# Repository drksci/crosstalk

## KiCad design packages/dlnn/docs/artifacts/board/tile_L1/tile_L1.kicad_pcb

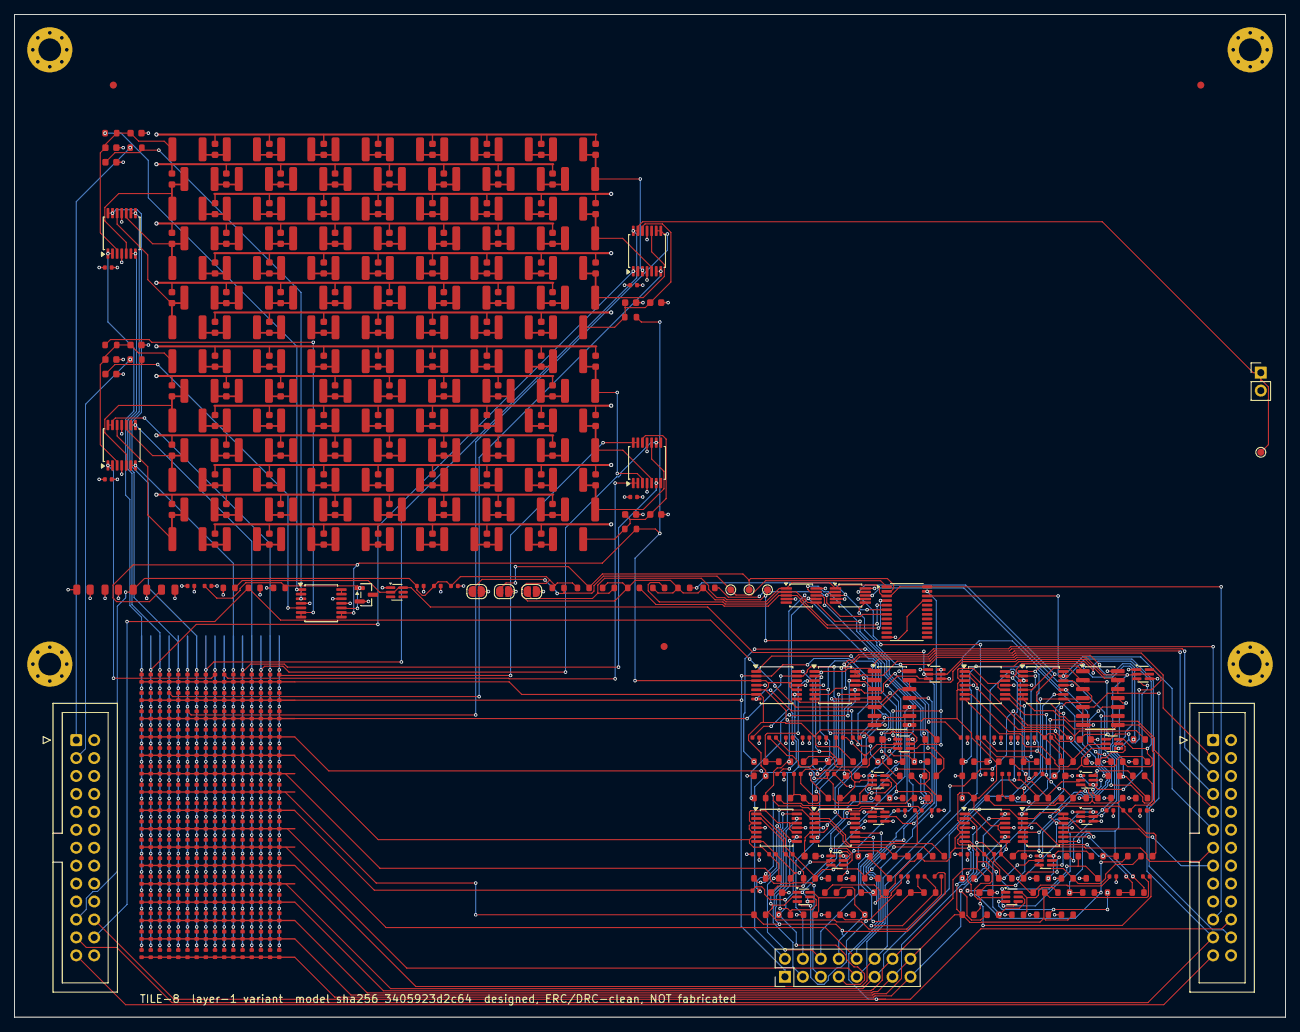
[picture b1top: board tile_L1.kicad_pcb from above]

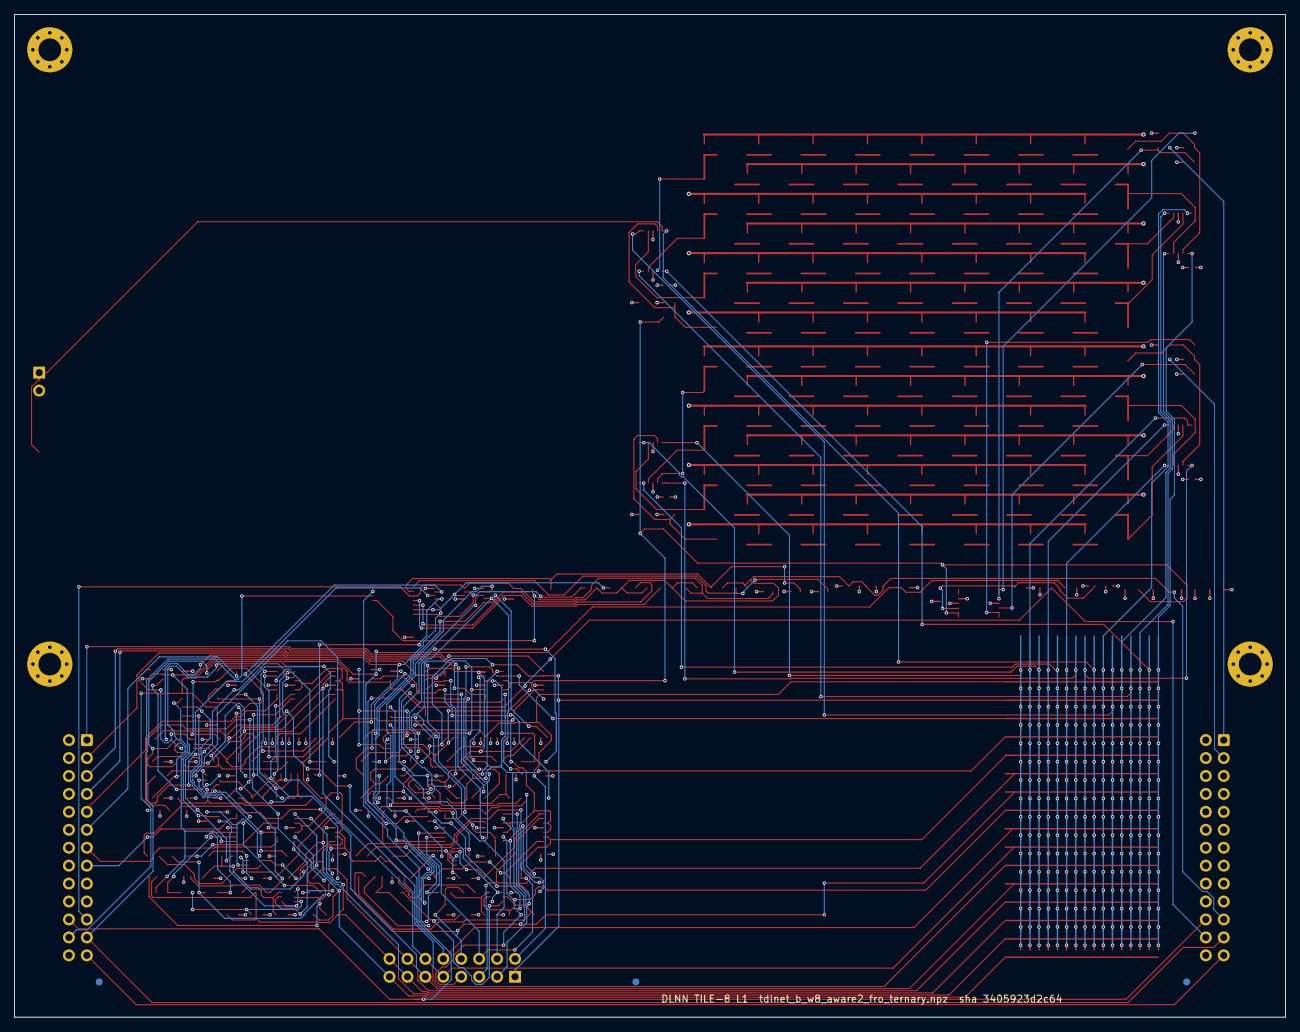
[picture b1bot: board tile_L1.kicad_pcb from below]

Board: 4 copper layers, 180.0 x 142.0 mm, 700 parts (3 on the bottom side), 258 nets.

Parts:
C0_0_1, C0_0_2, C0_56_1, C0_56_2, C1_0_1, C1_0_2, C1_56_1, C1_56_2: 30p; C_0603_1608Metric
C0_1, C0_2, C0_3, C0_4, C0_5, C0_6, C0_7, C0_8, C0_9, C0_10, C0_11, C0_12, C0_13, C0_14, C0_15, C0_16, C0_17, C0_18, C0_19, C0_20, C0_21, C0_22, C0_23, C0_24, C0_25, C0_26, C0_27, C0_28, C0_29, C0_30, C0_31, C0_32, C0_33, C0_34, C0_35, C0_36, C0_37, C0_38, C0_39, C0_40, C0_41, C0_42, C0_43, C0_44, C0_45, C0_46, C0_47, C0_48, C0_49, C0_50, C0_51, C0_52, C0_53, C0_54, C0_55, C1_1, C1_2, C1_3, C1_4, C1_5, C1_6, C1_7, C1_8, C1_9, C1_10, C1_11, C1_12, C1_13, C1_14, C1_15, C1_16, C1_17, C1_18, C1_19, C1_20, C1_21, C1_22, C1_23, C1_24, C1_25, C1_26, C1_27, C1_28, C1_29, C1_30, C1_31, C1_32, C1_33, C1_34, C1_35, C1_36, C1_37, C1_38, C1_39, C1_40, C1_41, C1_42, C1_43, C1_44, C1_45, C1_46, C1_47, C1_48, C1_49, C1_50, C1_51, C1_52, C1_53, C1_54, C1_55: 120p; C_0603_1608Metric
CB1, CB2, CB3, CB4: 10u; C_0805_2012Metric
CBF0, CBF1, CBF2, CBF3, CBF4, CBF5, CBF6, CBF7: 100n; C_0402_1005Metric
CDA0, CDA1, CDA2, CDA3, CDA4, CDA5, CDA6, CDA7: 8.2p; C_0402_1005Metric
CDCS0, CDCS1, CDCS2, CDCS3: 100n; C_0402_1005Metric
CDDA0, CDDA1, CDDA2, CDDA3: 100n; C_0402_1005Metric
CDDAC0, CDDAC1: 100n; C_0402_1005Metric
CDIB0: 100n; C_0402_1005Metric
CDMUX1: 100n; C_0402_1005Metric
CDSH0, CDSH1: 100n; C_0402_1005Metric
CDTA0, CDTA1: 100n; C_0402_1005Metric
CDTB0, CDTB1: 100n; C_0402_1005Metric
CFN0, CFN1, CFN2, CFN3, CFN4, CFN5, CFN6, CFN7: 15p; C_0402_1005Metric
CFP0, CFP1, CFP2, CFP3, CFP4, CFP5, CFP6, CFP7: 15p; C_0402_1005Metric
CH0, CH1, CH2, CH3, CH4, CH5, CH6, CH7: 560p; C_0603_1608Metric
CP0, CP1: 330p; C_0603_1608Metric
CREF1: 100n; C_0402_1005Metric
FID1, FID2, FID3, FID4, FID5, FID6: Fiducial_1mm_Mask2mm
H1, H2, H3, H4: MountingHole_3.2mm_M3_Pad_Via
JIN1: 2x13 IDC; IDC-Header_2x13_P2.54mm_Vertical
JMON1: MON; PinHeader_1x02_P2.54mm_Vertical
JOUT1: 2x13 IDC; IDC-Header_2x13_P2.54mm_Vertical
JPID0, JPID1, JPID2: ID; SolderJumper-2_P1.3mm_Open_RoundedPad1.0x1.5mm
JPS1: J_PS 2x8; PinHeader_2x08_P2.54mm_Vertical
L0_1, L0_2, L0_3, L0_4, L0_5, L0_6, L0_7, L0_8, L0_9, L0_10, L0_11, L0_12, L0_13, L0_14, L0_15, L0_16, L0_17, L0_18, L0_19, L0_20, L0_21, L0_22, L0_23, L0_24, L0_25, L0_26, L0_27, L0_28, L0_29, L0_30, L0_31, L0_32, L0_33, L0_34, L0_35, L0_36, L0_37, L0_38, L0_39, L0_40, L0_41, L0_42, L0_43, L0_44, L0_45, L0_46, L0_47, L0_48, L0_49, L0_50, L0_51, L0_52, L0_53, L0_54, L0_55, L0_56, L1_1, L1_2, L1_3, L1_4, L1_5, L1_6, L1_7, L1_8, L1_9, L1_10, L1_11, L1_12, L1_13, L1_14, L1_15, L1_16, L1_17, L1_18, L1_19, L1_20, L1_21, L1_22, L1_23, L1_24, L1_25, L1_26, L1_27, L1_28, L1_29, L1_30, L1_31, L1_32, L1_33, L1_34, L1_35, L1_36, L1_37, L1_38, L1_39, L1_40, L1_41, L1_42, L1_43, L1_44, L1_45, L1_46, L1_47, L1_48, L1_49, L1_50, L1_51, L1_52, L1_53, L1_54, L1_55, L1_56: 120u; L_1812_4532Metric
QD0, QD1, QD2, QD3, QD4, QD5, QD6, QD7: BCM847BS; SOT-363_SC-70-6
RB0, RB1, RB2, RB3, RB4, RB5, RB6, RB7: 15k; R_0603_1608Metric
RDA1_0, RDA1_1, RDA1_2, RDA1_3, RDA1_4, RDA1_5, RDA1_6, RDA1_7, RDA3_0, RDA3_1, RDA3_2, RDA3_3, RDA3_4, RDA3_5, RDA3_6, RDA3_7: 20k; R_0603_1608Metric
RDA2_0, RDA2_1, RDA2_2, RDA2_3, RDA2_4, RDA2_5, RDA2_6, RDA2_7, RDA4_0, RDA4_1, RDA4_2, RDA4_3, RDA4_4, RDA4_5, RDA4_6, RDA4_7: 10.5k; R_0603_1608Metric
RFN0, RFN1, RFN2, RFN3, RFN4, RFN5, RFN6, RFN7: 2.21k; R_0603_1608Metric
RFP0, RFP1, RFP2, RFP3, RFP4, RFP5, RFP6, RFP7: 2.21k; R_0603_1608Metric
RID0, RID1, RID2: 10k; R_0603_1608Metric
RLD1_0, RLD1_1, RLD1_2, RLD1_3, RLD1_4, RLD1_5, RLD1_6, RLD1_7, RLD2_0, RLD2_1, RLD2_2, RLD2_3, RLD2_4, RLD2_5, RLD2_6, RLD2_7: 1k; R_0603_1608Metric
RMIR1: 4.32k; R_0603_1608Metric
RO0, RO1, RO2, RO3, RO4, RO5, RO6, RO7: 25.5k; R_0603_1608Metric
RP0, RP1: 1k; R_0603_1608Metric
RPD1: 10k; R_0603_1608Metric
RPU1, RPU2, RPU3, RPU4: 10k; R_0603_1608Metric
RREF1: 2.49k; R_0603_1608Metric
RS0, RS1: 1k; R_0603_1608Metric
RT0, RT1: 1k; R_0603_1608Metric
RXN_0_0_0, RXN_0_0_1, RXN_0_0_2, RXN_0_0_3, RXN_0_0_4, RXN_0_0_5, RXN_0_0_6, RXN_0_0_7, RXN_0_1_0, RXN_0_1_1, RXN_0_1_2, RXN_0_1_3, RXN_0_1_4, RXN_0_1_5, RXN_0_1_6, RXN_0_1_7, RXN_1_0_0, RXN_1_0_1, RXN_1_0_2, RXN_1_0_3, RXN_1_0_4, RXN_1_0_5, RXN_1_0_6, RXN_1_0_7, RXN_1_1_0, RXN_1_1_1, RXN_1_1_2, RXN_1_1_3, RXN_1_1_4, RXN_1_1_5, RXN_1_1_6, RXN_1_1_7, RXN_2_0_0, RXN_2_0_1, RXN_2_0_2, RXN_2_0_3, RXN_2_0_4, RXN_2_0_5, RXN_2_0_6, RXN_2_0_7, RXN_2_1_0, RXN_2_1_1, RXN_2_1_2, RXN_2_1_3, RXN_2_1_4, RXN_2_1_5, RXN_2_1_6, RXN_2_1_7, RXN_3_0_0, RXN_3_0_1, RXN_3_0_2, RXN_3_0_3, RXN_3_0_4, RXN_3_0_5, RXN_3_0_6, RXN_3_0_7, RXN_3_1_0, RXN_3_1_1, RXN_3_1_2, RXN_3_1_3, RXN_3_1_4, RXN_3_1_5, RXN_3_1_6, RXN_3_1_7, RXN_4_0_0, RXN_4_0_1, RXN_4_0_2, RXN_4_0_3, RXN_4_0_4, RXN_4_0_5, RXN_4_0_6, RXN_4_0_7, RXN_4_1_0, RXN_4_1_1, RXN_4_1_2, RXN_4_1_3, RXN_4_1_4, RXN_4_1_5, RXN_4_1_6, RXN_4_1_7, RXN_5_0_0, RXN_5_0_1, RXN_5_0_2, RXN_5_0_3, RXN_5_0_4, RXN_5_0_5, RXN_5_0_6, RXN_5_0_7, RXN_5_1_0, RXN_5_1_1, RXN_5_1_2, RXN_5_1_3, RXN_5_1_4, RXN_5_1_5, RXN_5_1_6, RXN_5_1_7, RXN_6_0_0, RXN_6_0_1, RXN_6_0_2, RXN_6_0_3, RXN_6_0_4, RXN_6_0_5, RXN_6_0_6, RXN_6_0_7, RXN_6_1_0, RXN_6_1_1, RXN_6_1_2, RXN_6_1_3, RXN_6_1_4, RXN_6_1_5, RXN_6_1_6, RXN_6_1_7, RXN_7_0_0, RXN_7_0_1, RXN_7_0_2, RXN_7_0_3, RXN_7_0_4, RXN_7_0_5, RXN_7_0_6, RXN_7_0_7, RXN_7_1_0, RXN_7_1_1, RXN_7_1_2, RXN_7_1_3, RXN_7_1_4, RXN_7_1_5, RXN_7_1_6, RXN_7_1_7: 10k; R_0402_1005Metric
RXP_0_0_0, RXP_0_0_1, RXP_0_0_2, RXP_0_0_3, RXP_0_0_4, RXP_0_0_5, RXP_0_0_6, RXP_0_0_7, RXP_0_1_0, RXP_0_1_1, RXP_0_1_2, RXP_0_1_3, RXP_0_1_4, RXP_0_1_5, RXP_0_1_6, RXP_0_1_7, RXP_1_0_0, RXP_1_0_1, RXP_1_0_2, RXP_1_0_3, RXP_1_0_4, RXP_1_0_5, RXP_1_0_6, RXP_1_0_7, RXP_1_1_0, RXP_1_1_1, RXP_1_1_2, RXP_1_1_3, RXP_1_1_4, RXP_1_1_5, RXP_1_1_6, RXP_1_1_7, RXP_2_0_0, RXP_2_0_1, RXP_2_0_2, RXP_2_0_3, RXP_2_0_4, RXP_2_0_5, RXP_2_0_6, RXP_2_0_7, RXP_2_1_0, RXP_2_1_1, RXP_2_1_2, RXP_2_1_3, RXP_2_1_4, RXP_2_1_5, RXP_2_1_6, RXP_2_1_7, RXP_3_0_0, RXP_3_0_1, RXP_3_0_2, RXP_3_0_3, RXP_3_0_4, RXP_3_0_5, RXP_3_0_6, RXP_3_0_7, RXP_3_1_0, RXP_3_1_1, RXP_3_1_2, RXP_3_1_3, RXP_3_1_4, RXP_3_1_5, RXP_3_1_6, RXP_3_1_7, RXP_4_0_0, RXP_4_0_1, RXP_4_0_2, RXP_4_0_3, RXP_4_0_4, RXP_4_0_5, RXP_4_0_6, RXP_4_0_7, RXP_4_1_0, RXP_4_1_1, RXP_4_1_2, RXP_4_1_3, RXP_4_1_4, RXP_4_1_5, RXP_4_1_6, RXP_4_1_7, RXP_5_0_0, RXP_5_0_1, RXP_5_0_2, RXP_5_0_3, RXP_5_0_4, RXP_5_0_5, RXP_5_0_6, RXP_5_0_7, RXP_5_1_0, RXP_5_1_1, RXP_5_1_2, RXP_5_1_3, RXP_5_1_4, RXP_5_1_5, RXP_5_1_6, RXP_5_1_7, RXP_6_0_0, RXP_6_0_1, RXP_6_0_2, RXP_6_0_3, RXP_6_0_4, RXP_6_0_5, RXP_6_0_6, RXP_6_0_7, RXP_6_1_0, RXP_6_1_1, RXP_6_1_2, RXP_6_1_3, RXP_6_1_4, RXP_6_1_5, RXP_6_1_6, RXP_6_1_7, RXP_7_0_0, RXP_7_0_1, RXP_7_0_2, RXP_7_0_3, RXP_7_0_4, RXP_7_0_5, RXP_7_0_6, RXP_7_0_7, RXP_7_1_0, RXP_7_1_1, RXP_7_1_2, RXP_7_1_3, RXP_7_1_4, RXP_7_1_5, RXP_7_1_6, RXP_7_1_7: 10k; R_0402_1005Metric
TPID0: TID0; TestPoint_Pad_D1.0mm
TPID1: TID1; TestPoint_Pad_D1.0mm
TPID2: TID2; TestPoint_Pad_D1.0mm
TPMON1: MON; TestPoint_Pad_D1.0mm
UCS0, UCS1, UCS2, UCS3: TLV9064IPW; TSSOP-14_4.4x5mm_P0.65mm
UDA0, UDA1, UDA2, UDA3: TLV9064IPW; TSSOP-14_4.4x5mm_P0.65mm
UDAC0, UDAC1: MCP4728; MSOP-10_3x3mm_P0.5mm
UIB0: TLV9064IPW; TSSOP-14_4.4x5mm_P0.65mm
UMUX1: TCA9548APWR; TSSOP-24_4.4x7.8mm_P0.65mm
UREF1: LM4040B25FTA; SOT-23
USH0, USH1: 74HCT4066; SOIC-14_3.9x8.7mm_P1.27mm
UT0, UT1, UT2, UT3: BC847BS; SOT-363_SC-70-6
UTA0, UTA1: TLV9064IPW; TSSOP-14_4.4x5mm_P0.65mm
UTB0, UTB1: TLV9064IPW; TSSOP-14_4.4x5mm_P0.65mm
UTR1: BC847BS; SOT-363_SC-70-6

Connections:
+3V3: CB3.1, CDDAC0.1, CDDAC1.1, CDMUX1.1, JIN1.21, JOUT1.21, RID0.1, RID1.1, RID2.1, RPU1.1, RPU2.1, RPU3.1, RPU4.1, UDAC0.1, UDAC1.1, UMUX1.3, UMUX1.24
+5VA: CB1.1, CB2.1, CDCS0.1, CDCS1.1, CDCS2.1, CDCS3.1, CDDA0.1, CDDA1.1, CDDA2.1, CDDA3.1, CDIB0.1, CDSH0.1, CDSH1.1, CDTA0.1, CDTA1.1, CDTB0.1, CDTB1.1, JIN1.17, JIN1.19, JOUT1.17, JOUT1.19, RLD1_0.1, RLD1_1.1, RLD1_2.1, RLD1_3.1, RLD1_4.1, RLD1_5.1, RLD1_6.1, RLD1_7.1, RLD2_0.1, RLD2_1.1, RLD2_2.1, RLD2_3.1, RLD2_4.1, RLD2_5.1, RLD2_6.1, RLD2_7.1, RMIR1.1, RO0.1, RO1.1, RO2.1, RO3.1, RO4.1, RO5.1, RO6.1, RO7.1, RREF1.1, UCS0.4, UCS1.4, UCS2.4, UCS3.4, UDA0.4, UDA1.4, UDA2.4, UDA3.4, UIB0.4, USH0.14, USH1.14, UTA0.4, UTA1.4, UTB0.4, UTB1.4
/ch0/DAIN: CDA0.1, RDA3_0.2, RDA4_0.1, UDA0.2
/ch0/DAIP: RDA1_0.2, RDA2_0.1, UDA0.3
/ch0/DAO: CDA0.2, RDA4_0.2, UDA0.1, USH0.1
/ch0/DC1: QD0.6, RDA1_0.1, RLD1_0.2
/ch0/DC2: QD0.3, RDA3_0.1, RLD2_0.2
/ch0/HOLD: CH0.1, UDA0.5, USH0.2
/ch0/ON: CFN0.2, QD0.2, RFN0.2, UCS0.7
/ch0/OP: CFP0.2, QD0.5, RFP0.2, UCS0.1
/ch0/TAIL: QD0.1, QD0.4, UT0.6
/ch1/DAIN: CDA1.1, RDA3_1.2, RDA4_1.1, UDA0.9
/ch1/DAIP: RDA1_1.2, RDA2_1.1, UDA0.10
/ch1/DAO: CDA1.2, RDA4_1.2, UDA0.8, USH0.4
/ch1/DC1: QD1.6, RDA1_1.1, RLD1_1.2
/ch1/DC2: QD1.3, RDA3_1.1, RLD2_1.2
/ch1/HOLD: CH1.1, UDA0.12, USH0.3
/ch1/ON: CFN1.2, QD1.2, RFN1.2, UCS0.14
/ch1/OP: CFP1.2, QD1.5, RFP1.2, UCS0.8
/ch1/TAIL: QD1.1, QD1.4, UT0.3
/ch2/DAIN: CDA2.1, RDA3_2.2, RDA4_2.1, UDA1.2
/ch2/DAIP: RDA1_2.2, RDA2_2.1, UDA1.3
/ch2/DAO: CDA2.2, RDA4_2.2, UDA1.1, USH0.8
/ch2/DC1: QD2.6, RDA1_2.1, RLD1_2.2
/ch2/DC2: QD2.3, RDA3_2.1, RLD2_2.2
/ch2/HOLD: CH2.1, UDA1.5, USH0.9
/ch2/ON: CFN2.2, QD2.2, RFN2.2, UCS1.7
/ch2/OP: CFP2.2, QD2.5, RFP2.2, UCS1.1
/ch2/TAIL: QD2.1, QD2.4, UT1.6
/ch3/DAIN: CDA3.1, RDA3_3.2, RDA4_3.1, UDA1.9
/ch3/DAIP: RDA1_3.2, RDA2_3.1, UDA1.10
/ch3/DAO: CDA3.2, RDA4_3.2, UDA1.8, USH0.11
/ch3/DC1: QD3.6, RDA1_3.1, RLD1_3.2
/ch3/DC2: QD3.3, RDA3_3.1, RLD2_3.2
/ch3/HOLD: CH3.1, UDA1.12, USH0.10
/ch3/ON: CFN3.2, QD3.2, RFN3.2, UCS1.14
/ch3/OP: CFP3.2, QD3.5, RFP3.2, UCS1.8
/ch3/TAIL: QD3.1, QD3.4, UT1.3
/ch4/DAIN: CDA4.1, RDA3_4.2, RDA4_4.1, UDA2.2
/ch4/DAIP: RDA1_4.2, RDA2_4.1, UDA2.3
/ch4/DAO: CDA4.2, RDA4_4.2, UDA2.1, USH1.1
/ch4/DC1: QD4.6, RDA1_4.1, RLD1_4.2
/ch4/DC2: QD4.3, RDA3_4.1, RLD2_4.2
/ch4/HOLD: CH4.1, UDA2.5, USH1.2
/ch4/ON: CFN4.2, QD4.2, RFN4.2, UCS2.7
/ch4/OP: CFP4.2, QD4.5, RFP4.2, UCS2.1
/ch4/TAIL: QD4.1, QD4.4, UT2.6
/ch5/DAIN: CDA5.1, RDA3_5.2, RDA4_5.1, UDA2.9
/ch5/DAIP: RDA1_5.2, RDA2_5.1, UDA2.10
/ch5/DAO: CDA5.2, RDA4_5.2, UDA2.8, USH1.4
/ch5/DC1: QD5.6, RDA1_5.1, RLD1_5.2
/ch5/DC2: QD5.3, RDA3_5.1, RLD2_5.2
/ch5/HOLD: CH5.1, UDA2.12, USH1.3
/ch5/ON: CFN5.2, QD5.2, RFN5.2, UCS2.14
/ch5/OP: CFP5.2, QD5.5, RFP5.2, UCS2.8
/ch5/TAIL: QD5.1, QD5.4, UT2.3
/ch6/DAIN: CDA6.1, RDA3_6.2, RDA4_6.1, UDA3.2
/ch6/DAIP: RDA1_6.2, RDA2_6.1, UDA3.3
/ch6/DAO: CDA6.2, RDA4_6.2, UDA3.1, USH1.8
/ch6/DC1: QD6.6, RDA1_6.1, RLD1_6.2
/ch6/DC2: QD6.3, RDA3_6.1, RLD2_6.2
/ch6/HOLD: CH6.1, UDA3.5, USH1.9
/ch6/ON: CFN6.2, QD6.2, RFN6.2, UCS3.7
/ch6/OP: CFP6.2, QD6.5, RFP6.2, UCS3.1
/ch6/TAIL: QD6.1, QD6.4, UT3.6
/ch7/DAIN: CDA7.1, RDA3_7.2, RDA4_7.1, UDA3.9
/ch7/DAIP: RDA1_7.2, RDA2_7.1, UDA3.10
/ch7/DAO: CDA7.2, RDA4_7.2, UDA3.8, USH1.11
/ch7/DC1: QD7.6, RDA1_7.1, RLD1_7.2
/ch7/DC2: QD7.3, RDA3_7.1, RLD2_7.2
/ch7/HOLD: CH7.1, UDA3.12, USH1.10
/ch7/ON: CFN7.2, QD7.2, RFN7.2, UCS3.14
/ch7/OP: CFP7.2, QD7.5, RFP7.2, UCS3.8
/ch7/TAIL: QD7.1, QD7.4, UT3.3
/connectors/SCL0: RPU2.2, UDAC0.2, UMUX1.5
/connectors/SCL1: RPU4.2, UDAC1.2, UMUX1.7
/connectors/SDA0: RPU1.2, UDAC0.3, UMUX1.4
/connectors/SDA1: RPU3.2, UDAC1.3, UMUX1.6
/connectors/TID0: JPID0.1, RID0.2, TPID0.1, UMUX1.1
/connectors/TID1: JPID1.1, RID1.2, TPID1.1, UMUX1.2
/connectors/TID2: JPID2.1, RID2.2, TPID2.1, UMUX1.21
/line0/IB: RS0.1, UIB0.1, UIB0.2
/line0/N0: C0_0_1.1, C0_0_2.1, L0_1.1, RS0.2, UTA0.3
/line0/N8: C0_8.1, L0_8.2, L0_9.1, UTB0.3
/line0/N16: C0_16.1, L0_16.2, L0_17.1, UTA0.5
/line0/N24: C0_24.1, L0_24.2, L0_25.1, UTB0.5
/line0/N28: C0_28.1, L0_28.2, L0_29.1
/line0/N32: C0_32.1, L0_32.2, L0_33.1, UTA0.10
/line0/N40: C0_40.1, L0_40.2, L0_41.1, UTB0.10
/line0/N48: C0_48.1, L0_48.2, L0_49.1, UTA0.12
/line0/N56: C0_56_1.1, C0_56_2.1, L0_56.2, RT0.1, UTB0.12
/line0/RC: CP0.1, RP0.2, UIB0.3
/line1/IB: RS1.1, UIB0.6, UIB0.7
/line1/N0: C1_0_1.1, C1_0_2.1, L1_1.1, RS1.2, UTA1.3
/line1/N8: C1_8.1, L1_8.2, L1_9.1, UTB1.3
/line1/N16: C1_16.1, L1_16.2, L1_17.1, UTA1.5
/line1/N24: C1_24.1, L1_24.2, L1_25.1, UTB1.5
/line1/N28: C1_28.1, L1_28.2, L1_29.1
/line1/N32: C1_32.1, L1_32.2, L1_33.1, UTA1.10
/line1/N40: C1_40.1, L1_40.2, L1_41.1, UTB1.10
/line1/N48: C1_48.1, L1_48.2, L1_49.1, UTA1.12
/line1/N56: C1_56_1.1, C1_56_2.1, L1_56.2, RT1.1, UTB1.12
/line1/RC: CP1.1, RP1.2, UIB0.5
/power/PK_UIB0_4: UIB0.13, UIB0.14
/power/V2R5: CREF1.1, RREF1.2, UIB0.10, UREF1.1
BIAS0: CBF0.1, RB0.1, UDAC0.6
BIAS1: CBF1.1, RB1.1, UDAC0.7
BIAS2: CBF2.1, RB2.1, UDAC0.8
BIAS3: CBF3.1, RB3.1, UDAC0.9
BIAS4: CBF4.1, RB4.1, UDAC1.6
BIAS5: CBF5.1, RB5.1, UDAC1.7
BIAS6: CBF6.1, RB6.1, UDAC1.8
BIAS7: CBF7.1, RB7.1, UDAC1.9
GND: C0_0_1.2, C0_0_2.2, C0_1.2, C0_2.2, C0_3.2, C0_4.2, C0_5.2, C0_6.2, C0_7.2, C0_8.2, C0_9.2, C0_10.2, C0_11.2, C0_12.2, C0_13.2, C0_14.2, C0_15.2, C0_16.2, C0_17.2, C0_18.2, C0_19.2, C0_20.2, C0_21.2, C0_22.2, C0_23.2, C0_24.2, C0_25.2, C0_26.2, C0_27.2, C0_28.2, C0_29.2, C0_30.2, C0_31.2, C0_32.2, C0_33.2, C0_34.2, C0_35.2, C0_36.2, C0_37.2, C0_38.2, C0_39.2, C0_40.2, C0_41.2, C0_42.2, C0_43.2, C0_44.2, C0_45.2, C0_46.2, C0_47.2, C0_48.2, C0_49.2, C0_50.2, C0_51.2, C0_52.2, C0_53.2, C0_54.2, C0_55.2, C0_56_1.2, C0_56_2.2, C1_0_1.2, C1_0_2.2, C1_1.2, C1_2.2, C1_3.2, C1_4.2, C1_5.2, C1_6.2, C1_7.2, C1_8.2, C1_9.2, C1_10.2, C1_11.2, C1_12.2, C1_13.2, C1_14.2, C1_15.2, C1_16.2, C1_17.2, C1_18.2, C1_19.2, C1_20.2, C1_21.2, C1_22.2, C1_23.2, C1_24.2, C1_25.2, C1_26.2, C1_27.2, C1_28.2, C1_29.2, C1_30.2, C1_31.2, C1_32.2, C1_33.2, C1_34.2, C1_35.2, C1_36.2, C1_37.2, C1_38.2, C1_39.2, C1_40.2, C1_41.2, C1_42.2, C1_43.2, C1_44.2, C1_45.2, C1_46.2, C1_47.2, C1_48.2, C1_49.2, C1_50.2, C1_51.2, C1_52.2, C1_53.2, C1_54.2, C1_55.2, C1_56_1.2, C1_56_2.2, CB1.2, CB2.2, CB3.2, CB4.2, CBF0.2, CBF1.2, CBF2.2, CBF3.2, CBF4.2, CBF5.2, CBF6.2, CBF7.2, CDCS0.2, CDCS1.2, CDCS2.2, CDCS3.2, CDDA0.2, CDDA1.2, CDDA2.2, CDDA3.2, CDDAC0.2, CDDAC1.2, CDIB0.2, CDMUX1.2, CDSH0.2, CDSH1.2, CDTA0.2, CDTA1.2, CDTB0.2, CDTB1.2, CH0.2, CH1.2, CH2.2, CH3.2, CH4.2, CH5.2, CH6.2, CH7.2, CP0.2, CP1.2, CREF1.2, H1.1, H2.1, H3.1, H4.1, JIN1.2, JIN1.4, JIN1.6, JIN1.8, JIN1.10, JIN1.12, JIN1.14, JIN1.16, JIN1.18, JIN1.20, JIN1.26, JMON1.2, JOUT1.2, JOUT1.4, JOUT1.6, JOUT1.8, JOUT1.10, JOUT1.12, JOUT1.14, JOUT1.16, JOUT1.18, JOUT1.20, JOUT1.26, JPID0.2, JPID1.2, JPID2.2, RPD1.2, UCS0.11, UCS1.11, UCS2.11, UCS3.11, UDA0.11, UDA1.11, UDA2.11, UDA3.11, UDAC0.4, UDAC0.10, UDAC1.4, UDAC1.10, UIB0.11, UIB0.12, UMUX1.12, UREF1.2, USH0.7, USH1.7, UT0.1, UT0.4, UT1.1, UT1.4, UT2.1, UT2.4, UT3.1, UT3.4, UTA0.11, UTA1.11, UTB0.11, UTB1.11, UTR1.1
MIRB: RMIR1.2, UT0.2, UT0.5, UT1.2, UT1.5, UT2.2, UT2.5, UT3.2, UT3.5, UTR1.2, UTR1.6
unnamed: C0_1.1, L0_1.2, L0_2.1
unnamed: C0_2.1, L0_2.2, L0_3.1
unnamed: C0_3.1, L0_3.2, L0_4.1
unnamed: C0_4.1, L0_4.2, L0_5.1
unnamed: C0_5.1, L0_5.2, L0_6.1
unnamed: C0_6.1, L0_6.2, L0_7.1
unnamed: C0_7.1, L0_7.2, L0_8.1
unnamed: C0_9.1, L0_9.2, L0_10.1
unnamed: C0_10.1, L0_10.2, L0_11.1
unnamed: C0_11.1, L0_11.2, L0_12.1
unnamed: C0_12.1, L0_12.2, L0_13.1
unnamed: C0_13.1, L0_13.2, L0_14.1
unnamed: C0_14.1, L0_14.2, L0_15.1
unnamed: C0_15.1, L0_15.2, L0_16.1
unnamed: C0_17.1, L0_17.2, L0_18.1
unnamed: C0_18.1, L0_18.2, L0_19.1
unnamed: C0_19.1, L0_19.2, L0_20.1
unnamed: C0_20.1, L0_20.2, L0_21.1
unnamed: C0_21.1, L0_21.2, L0_22.1
unnamed: C0_22.1, L0_22.2, L0_23.1
unnamed: C0_23.1, L0_23.2, L0_24.1
unnamed: C0_25.1, L0_25.2, L0_26.1
unnamed: C0_26.1, L0_26.2, L0_27.1
unnamed: C0_27.1, L0_27.2, L0_28.1
unnamed: C0_29.1, L0_29.2, L0_30.1
unnamed: C0_30.1, L0_30.2, L0_31.1
unnamed: C0_31.1, L0_31.2, L0_32.1
unnamed: C0_33.1, L0_33.2, L0_34.1
unnamed: C0_34.1, L0_34.2, L0_35.1
unnamed: C0_35.1, L0_35.2, L0_36.1
unnamed: C0_36.1, L0_36.2, L0_37.1
unnamed: C0_37.1, L0_37.2, L0_38.1
unnamed: C0_38.1, L0_38.2, L0_39.1
unnamed: C0_39.1, L0_39.2, L0_40.1
unnamed: C0_41.1, L0_41.2, L0_42.1
unnamed: C0_42.1, L0_42.2, L0_43.1
unnamed: C0_43.1, L0_43.2, L0_44.1
unnamed: C0_44.1, L0_44.2, L0_45.1
unnamed: C0_45.1, L0_45.2, L0_46.1
unnamed: C0_46.1, L0_46.2, L0_47.1
unnamed: C0_47.1, L0_47.2, L0_48.1
unnamed: C0_49.1, L0_49.2, L0_50.1
unnamed: C0_50.1, L0_50.2, L0_51.1
unnamed: C0_51.1, L0_51.2, L0_52.1
unnamed: C0_52.1, L0_52.2, L0_53.1
unnamed: C0_53.1, L0_53.2, L0_54.1
unnamed: C0_54.1, L0_54.2, L0_55.1
unnamed: C0_55.1, L0_55.2, L0_56.1
unnamed: C1_1.1, L1_1.2, L1_2.1
unnamed: C1_2.1, L1_2.2, L1_3.1
unnamed: C1_3.1, L1_3.2, L1_4.1
unnamed: C1_4.1, L1_4.2, L1_5.1
unnamed: C1_5.1, L1_5.2, L1_6.1
unnamed: C1_6.1, L1_6.2, L1_7.1
unnamed: C1_7.1, L1_7.2, L1_8.1
unnamed: C1_9.1, L1_9.2, L1_10.1
unnamed: C1_10.1, L1_10.2, L1_11.1
unnamed: C1_11.1, L1_11.2, L1_12.1
unnamed: C1_12.1, L1_12.2, L1_13.1
unnamed: C1_13.1, L1_13.2, L1_14.1
unnamed: C1_14.1, L1_14.2, L1_15.1
unnamed: C1_15.1, L1_15.2, L1_16.1
unnamed: C1_17.1, L1_17.2, L1_18.1
unnamed: C1_18.1, L1_18.2, L1_19.1
unnamed: C1_19.1, L1_19.2, L1_20.1
unnamed: C1_20.1, L1_20.2, L1_21.1
unnamed: C1_21.1, L1_21.2, L1_22.1
unnamed: C1_22.1, L1_22.2, L1_23.1
unnamed: C1_23.1, L1_23.2, L1_24.1
unnamed: C1_25.1, L1_25.2, L1_26.1
unnamed: C1_26.1, L1_26.2, L1_27.1
unnamed: C1_27.1, L1_27.2, L1_28.1
unnamed: C1_29.1, L1_29.2, L1_30.1
unnamed: C1_30.1, L1_30.2, L1_31.1
unnamed: C1_31.1, L1_31.2, L1_32.1
unnamed: C1_33.1, L1_33.2, L1_34.1
unnamed: C1_34.1, L1_34.2, L1_35.1
unnamed: C1_35.1, L1_35.2, L1_36.1
unnamed: C1_36.1, L1_36.2, L1_37.1
unnamed: C1_37.1, L1_37.2, L1_38.1
unnamed: C1_38.1, L1_38.2, L1_39.1
unnamed: C1_39.1, L1_39.2, L1_40.1
unnamed: C1_41.1, L1_41.2, L1_42.1
unnamed: C1_42.1, L1_42.2, L1_43.1
unnamed: C1_43.1, L1_43.2, L1_44.1
unnamed: C1_44.1, L1_44.2, L1_45.1
unnamed: C1_45.1, L1_45.2, L1_46.1
unnamed: C1_46.1, L1_46.2, L1_47.1
unnamed: C1_47.1, L1_47.2, L1_48.1
unnamed: C1_49.1, L1_49.2, L1_50.1
unnamed: C1_50.1, L1_50.2, L1_51.1
unnamed: C1_51.1, L1_51.2, L1_52.1
unnamed: C1_52.1, L1_52.2, L1_53.1
unnamed: C1_53.1, L1_53.2, L1_54.1
unnamed: C1_54.1, L1_54.2, L1_55.1
unnamed: C1_55.1, L1_55.2, L1_56.1
OUT0: JOUT1.1, UDA0.6, UDA0.7
OUT1: JOUT1.3, UDA0.13, UDA0.14
OUT2: JOUT1.5, UDA1.6, UDA1.7
OUT3: JOUT1.7, UDA1.13, UDA1.14
OUT4: JOUT1.9, UDA2.6, UDA2.7
OUT5: JOUT1.11, UDA2.13, UDA2.14
OUT6: JOUT1.13, UDA3.6, UDA3.7
OUT7: JOUT1.15, UDA3.13, UDA3.14
SCL: JIN1.23, JOUT1.23, UMUX1.22
SDA: JIN1.22, JOUT1.22, UMUX1.23
SH_CLK: JIN1.24, JOUT1.24, RPD1.1, USH0.5, USH0.6, USH0.12, USH0.13, USH1.5, USH1.6, USH1.12, USH1.13
SIG0: JIN1.1, RP0.1
SIG1: JIN1.3, RP1.1
SN0: CFN0.1, JPS1.2, RB0.2, RFN0.1, RO0.2, RXP_0_0_0.2, RXP_0_0_1.2, RXP_0_0_2.2, RXP_0_0_3.2, RXP_0_0_4.2, RXP_0_0_5.2, RXP_0_0_6.2, RXP_0_0_7.2, RXP_0_1_0.2, RXP_0_1_1.2, RXP_0_1_2.2, RXP_0_1_3.2, RXP_0_1_4.2, RXP_0_1_5.2, RXP_0_1_6.2, RXP_0_1_7.2, UCS0.6
SN1: CFN1.1, JPS1.4, RB1.2, RFN1.1, RO1.2, RXP_1_0_0.2, RXP_1_0_1.2, RXP_1_0_2.2, RXP_1_0_3.2, RXP_1_0_4.2, RXP_1_0_5.2, RXP_1_0_6.2, RXP_1_0_7.2, RXP_1_1_0.2, RXP_1_1_1.2, RXP_1_1_2.2, RXP_1_1_3.2, RXP_1_1_4.2, RXP_1_1_5.2, RXP_1_1_6.2, RXP_1_1_7.2, UCS0.13
SN2: CFN2.1, JPS1.6, RB2.2, RFN2.1, RO2.2, RXP_2_0_0.2, RXP_2_0_1.2, RXP_2_0_2.2, RXP_2_0_3.2, RXP_2_0_4.2, RXP_2_0_5.2, RXP_2_0_6.2, RXP_2_0_7.2, RXP_2_1_0.2, RXP_2_1_1.2, RXP_2_1_2.2, RXP_2_1_3.2, RXP_2_1_4.2, RXP_2_1_5.2, RXP_2_1_6.2, RXP_2_1_7.2, UCS1.6
SN3: CFN3.1, JPS1.8, RB3.2, RFN3.1, RO3.2, RXP_3_0_0.2, RXP_3_0_1.2, RXP_3_0_2.2, RXP_3_0_3.2, RXP_3_0_4.2, RXP_3_0_5.2, RXP_3_0_6.2, RXP_3_0_7.2, RXP_3_1_0.2, RXP_3_1_1.2, RXP_3_1_2.2, RXP_3_1_3.2, RXP_3_1_4.2, RXP_3_1_5.2, RXP_3_1_6.2, RXP_3_1_7.2, UCS1.13
SN4: CFN4.1, JPS1.10, RB4.2, RFN4.1, RO4.2, RXP_4_0_0.2, RXP_4_0_1.2, RXP_4_0_2.2, RXP_4_0_3.2, RXP_4_0_4.2, RXP_4_0_5.2, RXP_4_0_6.2, RXP_4_0_7.2, RXP_4_1_0.2, RXP_4_1_1.2, RXP_4_1_2.2, RXP_4_1_3.2, RXP_4_1_4.2, RXP_4_1_5.2, RXP_4_1_6.2, RXP_4_1_7.2, UCS2.6
SN5: CFN5.1, JPS1.12, RB5.2, RFN5.1, RO5.2, RXP_5_0_0.2, RXP_5_0_1.2, RXP_5_0_2.2, RXP_5_0_3.2, RXP_5_0_4.2, RXP_5_0_5.2, RXP_5_0_6.2, RXP_5_0_7.2, RXP_5_1_0.2, RXP_5_1_1.2, RXP_5_1_2.2, RXP_5_1_3.2, RXP_5_1_4.2, RXP_5_1_5.2, RXP_5_1_6.2, RXP_5_1_7.2, UCS2.13
SN6: CFN6.1, JPS1.14, RB6.2, RFN6.1, RO6.2, RXP_6_0_0.2, RXP_6_0_1.2, RXP_6_0_2.2, RXP_6_0_3.2, RXP_6_0_4.2, RXP_6_0_5.2, RXP_6_0_6.2, RXP_6_0_7.2, RXP_6_1_0.2, RXP_6_1_1.2, RXP_6_1_2.2, RXP_6_1_3.2, RXP_6_1_4.2, RXP_6_1_5.2, RXP_6_1_6.2, RXP_6_1_7.2, UCS3.6
SN7: CFN7.1, JPS1.16, RB7.2, RFN7.1, RO7.2, RXP_7_0_0.2, RXP_7_0_1.2, RXP_7_0_2.2, RXP_7_0_3.2, RXP_7_0_4.2, RXP_7_0_5.2, RXP_7_0_6.2, RXP_7_0_7.2, RXP_7_1_0.2, RXP_7_1_1.2, RXP_7_1_2.2, RXP_7_1_3.2, RXP_7_1_4.2, RXP_7_1_5.2, RXP_7_1_6.2, RXP_7_1_7.2, UCS3.13
SP0: CFP0.1, JPS1.1, RFP0.1, RXN_0_0_0.2, RXN_0_0_1.2, RXN_0_0_2.2, RXN_0_0_3.2, RXN_0_0_4.2, RXN_0_0_5.2, RXN_0_0_6.2, RXN_0_0_7.2, RXN_0_1_0.2, RXN_0_1_1.2, RXN_0_1_2.2, RXN_0_1_3.2, RXN_0_1_4.2, RXN_0_1_5.2, RXN_0_1_6.2, RXN_0_1_7.2, UCS0.2
SP1: CFP1.1, JPS1.3, RFP1.1, RXN_1_0_0.2, RXN_1_0_1.2, RXN_1_0_2.2, RXN_1_0_3.2, RXN_1_0_4.2, RXN_1_0_5.2, RXN_1_0_6.2, RXN_1_0_7.2, RXN_1_1_0.2, RXN_1_1_1.2, RXN_1_1_2.2, RXN_1_1_3.2, RXN_1_1_4.2, RXN_1_1_5.2, RXN_1_1_6.2, RXN_1_1_7.2, UCS0.9
SP2: CFP2.1, JPS1.5, RFP2.1, RXN_2_0_0.2, RXN_2_0_1.2, RXN_2_0_2.2, RXN_2_0_3.2, RXN_2_0_4.2, RXN_2_0_5.2, RXN_2_0_6.2, RXN_2_0_7.2, RXN_2_1_0.2, RXN_2_1_1.2, RXN_2_1_2.2, RXN_2_1_3.2, RXN_2_1_4.2, RXN_2_1_5.2, RXN_2_1_6.2, RXN_2_1_7.2, UCS1.2
SP3: CFP3.1, JPS1.7, RFP3.1, RXN_3_0_0.2, RXN_3_0_1.2, RXN_3_0_2.2, RXN_3_0_3.2, RXN_3_0_4.2, RXN_3_0_5.2, RXN_3_0_6.2, RXN_3_0_7.2, RXN_3_1_0.2, RXN_3_1_1.2, RXN_3_1_2.2, RXN_3_1_3.2, RXN_3_1_4.2, RXN_3_1_5.2, RXN_3_1_6.2, RXN_3_1_7.2, UCS1.9
SP4: CFP4.1, JPS1.9, RFP4.1, RXN_4_0_0.2, RXN_4_0_1.2, RXN_4_0_2.2, RXN_4_0_3.2, RXN_4_0_4.2, RXN_4_0_5.2, RXN_4_0_6.2, RXN_4_0_7.2, RXN_4_1_0.2, RXN_4_1_1.2, RXN_4_1_2.2, RXN_4_1_3.2, RXN_4_1_4.2, RXN_4_1_5.2, RXN_4_1_6.2, RXN_4_1_7.2, UCS2.2
SP5: CFP5.1, JPS1.11, RFP5.1, RXN_5_0_0.2, RXN_5_0_1.2, RXN_5_0_2.2, RXN_5_0_3.2, RXN_5_0_4.2, RXN_5_0_5.2, RXN_5_0_6.2, RXN_5_0_7.2, RXN_5_1_0.2, RXN_5_1_1.2, RXN_5_1_2.2, RXN_5_1_3.2, RXN_5_1_4.2, RXN_5_1_5.2, RXN_5_1_6.2, RXN_5_1_7.2, UCS2.9
SP6: CFP6.1, JPS1.13, RFP6.1, RXN_6_0_0.2, RXN_6_0_1.2, RXN_6_0_2.2, RXN_6_0_3.2, RXN_6_0_4.2, RXN_6_0_5.2, RXN_6_0_6.2, RXN_6_0_7.2, RXN_6_1_0.2, RXN_6_1_1.2, RXN_6_1_2.2, RXN_6_1_3.2, RXN_6_1_4.2, RXN_6_1_5.2, RXN_6_1_6.2, RXN_6_1_7.2, UCS3.2
SP7: CFP7.1, JPS1.15, RFP7.1, RXN_7_0_0.2, RXN_7_0_1.2, RXN_7_0_2.2, RXN_7_0_3.2, RXN_7_0_4.2, RXN_7_0_5.2, RXN_7_0_6.2, RXN_7_0_7.2, RXN_7_1_0.2, RXN_7_1_1.2, RXN_7_1_2.2, RXN_7_1_3.2, RXN_7_1_4.2, RXN_7_1_5.2, RXN_7_1_6.2, RXN_7_1_7.2, UCS3.9
SYNC: JIN1.25, JOUT1.25
T0_0: RXN_0_0_0.1, RXN_1_0_0.1, RXN_2_0_0.1, RXN_3_0_0.1, RXN_4_0_0.1, RXN_5_0_0.1, RXN_6_0_0.1, RXN_7_0_0.1, RXP_0_0_0.1, RXP_1_0_0.1, RXP_2_0_0.1, RXP_3_0_0.1, RXP_4_0_0.1, RXP_5_0_0.1, RXP_6_0_0.1, RXP_7_0_0.1, UTA0.1, UTA0.2
T0_1: RXN_0_0_1.1, RXN_1_0_1.1, RXN_2_0_1.1, RXN_3_0_1.1, RXN_4_0_1.1, RXN_5_0_1.1, RXN_6_0_1.1, RXN_7_0_1.1, RXP_0_0_1.1, RXP_1_0_1.1, RXP_2_0_1.1, RXP_3_0_1.1, RXP_4_0_1.1, RXP_5_0_1.1, RXP_6_0_1.1, RXP_7_0_1.1, UTB0.1, UTB0.2
T0_2: RXN_0_0_2.1, RXN_1_0_2.1, RXN_2_0_2.1, RXN_3_0_2.1, RXN_4_0_2.1, RXN_5_0_2.1, RXN_6_0_2.1, RXN_7_0_2.1, RXP_0_0_2.1, RXP_1_0_2.1, RXP_2_0_2.1, RXP_3_0_2.1, RXP_4_0_2.1, RXP_5_0_2.1, RXP_6_0_2.1, RXP_7_0_2.1, UTA0.6, UTA0.7
T0_3: RXN_0_0_3.1, RXN_1_0_3.1, RXN_2_0_3.1, RXN_3_0_3.1, RXN_4_0_3.1, RXN_5_0_3.1, RXN_6_0_3.1, RXN_7_0_3.1, RXP_0_0_3.1, RXP_1_0_3.1, RXP_2_0_3.1, RXP_3_0_3.1, RXP_4_0_3.1, RXP_5_0_3.1, RXP_6_0_3.1, RXP_7_0_3.1, UTB0.6, UTB0.7
T0_4: RXN_0_0_4.1, RXN_1_0_4.1, RXN_2_0_4.1, RXN_3_0_4.1, RXN_4_0_4.1, RXN_5_0_4.1, RXN_6_0_4.1, RXN_7_0_4.1, RXP_0_0_4.1, RXP_1_0_4.1, RXP_2_0_4.1, RXP_3_0_4.1, RXP_4_0_4.1, RXP_5_0_4.1, RXP_6_0_4.1, RXP_7_0_4.1, UTA0.8, UTA0.9
T0_5: RXN_0_0_5.1, RXN_1_0_5.1, RXN_2_0_5.1, RXN_3_0_5.1, RXN_4_0_5.1, RXN_5_0_5.1, RXN_6_0_5.1, RXN_7_0_5.1, RXP_0_0_5.1, RXP_1_0_5.1, RXP_2_0_5.1, RXP_3_0_5.1, RXP_4_0_5.1, RXP_5_0_5.1, RXP_6_0_5.1, RXP_7_0_5.1, UTB0.8, UTB0.9
T0_6: RXN_0_0_6.1, RXN_1_0_6.1, RXN_2_0_6.1, RXN_3_0_6.1, RXN_4_0_6.1, RXN_5_0_6.1, RXN_6_0_6.1, RXN_7_0_6.1, RXP_0_0_6.1, RXP_1_0_6.1, RXP_2_0_6.1, RXP_3_0_6.1, RXP_4_0_6.1, RXP_5_0_6.1, RXP_6_0_6.1, RXP_7_0_6.1, UTA0.13, UTA0.14
T0_7: JMON1.1, RXN_0_0_7.1, RXN_1_0_7.1, RXN_2_0_7.1, RXN_3_0_7.1, RXN_4_0_7.1, RXN_5_0_7.1, RXN_6_0_7.1, RXN_7_0_7.1, RXP_0_0_7.1, RXP_1_0_7.1, RXP_2_0_7.1, RXP_3_0_7.1, RXP_4_0_7.1, RXP_5_0_7.1, RXP_6_0_7.1, RXP_7_0_7.1, TPMON1.1, UTB0.13, UTB0.14
T1_0: RXN_0_1_0.1, RXN_1_1_0.1, RXN_2_1_0.1, RXN_3_1_0.1, RXN_4_1_0.1, RXN_5_1_0.1, RXN_6_1_0.1, RXN_7_1_0.1, RXP_0_1_0.1, RXP_1_1_0.1, RXP_2_1_0.1, RXP_3_1_0.1, RXP_4_1_0.1, RXP_5_1_0.1, RXP_6_1_0.1, RXP_7_1_0.1, UTA1.1, UTA1.2
T1_1: RXN_0_1_1.1, RXN_1_1_1.1, RXN_2_1_1.1, RXN_3_1_1.1, RXN_4_1_1.1, RXN_5_1_1.1, RXN_6_1_1.1, RXN_7_1_1.1, RXP_0_1_1.1, RXP_1_1_1.1, RXP_2_1_1.1, RXP_3_1_1.1, RXP_4_1_1.1, RXP_5_1_1.1, RXP_6_1_1.1, RXP_7_1_1.1, UTB1.1, UTB1.2
T1_2: RXN_0_1_2.1, RXN_1_1_2.1, RXN_2_1_2.1, RXN_3_1_2.1, RXN_4_1_2.1, RXN_5_1_2.1, RXN_6_1_2.1, RXN_7_1_2.1, RXP_0_1_2.1, RXP_1_1_2.1, RXP_2_1_2.1, RXP_3_1_2.1, RXP_4_1_2.1, RXP_5_1_2.1, RXP_6_1_2.1, RXP_7_1_2.1, UTA1.6, UTA1.7
T1_3: RXN_0_1_3.1, RXN_1_1_3.1, RXN_2_1_3.1, RXN_3_1_3.1, RXN_4_1_3.1, RXN_5_1_3.1, RXN_6_1_3.1, RXN_7_1_3.1, RXP_0_1_3.1, RXP_1_1_3.1, RXP_2_1_3.1, RXP_3_1_3.1, RXP_4_1_3.1, RXP_5_1_3.1, RXP_6_1_3.1, RXP_7_1_3.1, UTB1.6, UTB1.7
T1_4: RXN_0_1_4.1, RXN_1_1_4.1, RXN_2_1_4.1, RXN_3_1_4.1, RXN_4_1_4.1, RXN_5_1_4.1, RXN_6_1_4.1, RXN_7_1_4.1, RXP_0_1_4.1, RXP_1_1_4.1, RXP_2_1_4.1, RXP_3_1_4.1, RXP_4_1_4.1, RXP_5_1_4.1, RXP_6_1_4.1, RXP_7_1_4.1, UTA1.8, UTA1.9
T1_5: RXN_0_1_5.1, RXN_1_1_5.1, RXN_2_1_5.1, RXN_3_1_5.1, RXN_4_1_5.1, RXN_5_1_5.1, RXN_6_1_5.1, RXN_7_1_5.1, RXP_0_1_5.1, RXP_1_1_5.1, RXP_2_1_5.1, RXP_3_1_5.1, RXP_4_1_5.1, RXP_5_1_5.1, RXP_6_1_5.1, RXP_7_1_5.1, UTB1.8, UTB1.9
T1_6: RXN_0_1_6.1, RXN_1_1_6.1, RXN_2_1_6.1, RXN_3_1_6.1, RXN_4_1_6.1, RXN_5_1_6.1, RXN_6_1_6.1, RXN_7_1_6.1, RXP_0_1_6.1, RXP_1_1_6.1, RXP_2_1_6.1, RXP_3_1_6.1, RXP_4_1_6.1, RXP_5_1_6.1, RXP_6_1_6.1, RXP_7_1_6.1, UTA1.13, UTA1.14
T1_7: RXN_0_1_7.1, RXN_1_1_7.1, RXN_2_1_7.1, RXN_3_1_7.1, RXN_4_1_7.1, RXN_5_1_7.1, RXN_6_1_7.1, RXN_7_1_7.1, RXP_0_1_7.1, RXP_1_1_7.1, RXP_2_1_7.1, RXP_3_1_7.1, RXP_4_1_7.1, RXP_5_1_7.1, RXP_6_1_7.1, RXP_7_1_7.1, UTB1.13, UTB1.14
VREF25: CB4.1, RDA2_0.2, RDA2_1.2, RDA2_2.2, RDA2_3.2, RDA2_4.2, RDA2_5.2, RDA2_6.2, RDA2_7.2, RT0.2, RT1.2, UCS0.3, UCS0.5, UCS0.10, UCS0.12, UCS1.3, UCS1.5, UCS1.10, UCS1.12, UCS2.3, UCS2.5, UCS2.10, UCS2.12, UCS3.3, UCS3.5, UCS3.10, UCS3.12, UIB0.8, UIB0.9
